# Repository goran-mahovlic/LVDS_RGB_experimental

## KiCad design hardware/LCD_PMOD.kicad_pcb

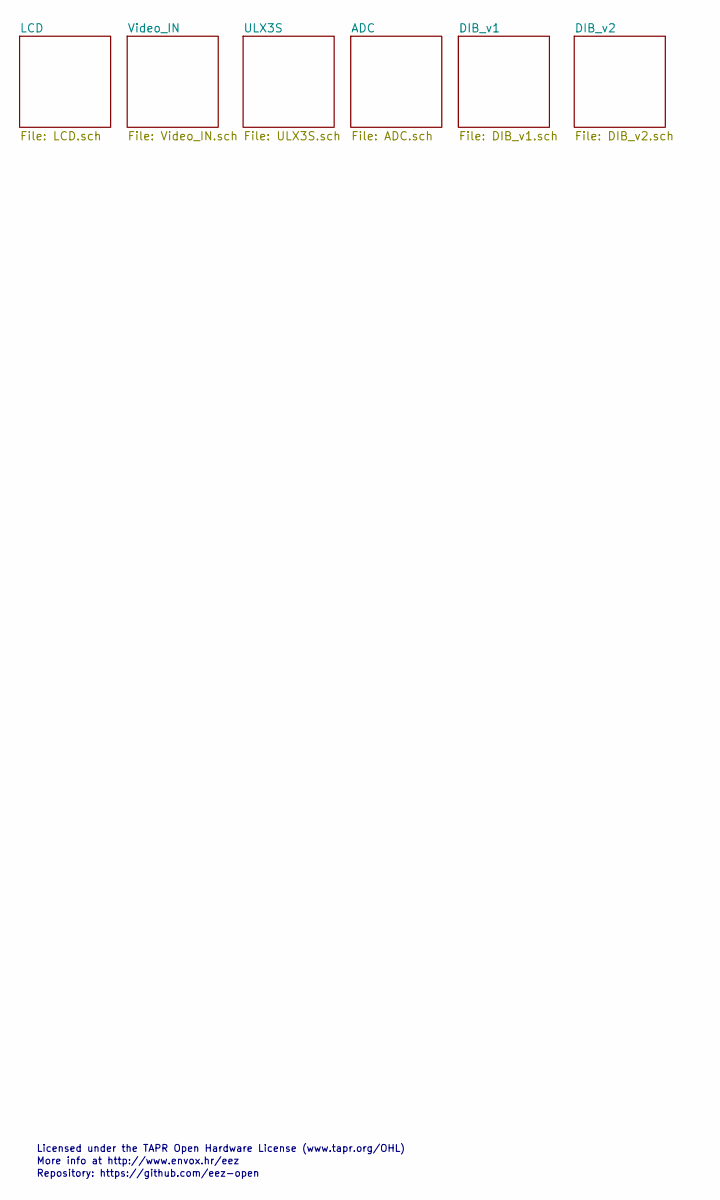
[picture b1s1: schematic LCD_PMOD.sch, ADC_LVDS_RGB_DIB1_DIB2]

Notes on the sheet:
Licensed under the TAPR Open Hardware License (www.tapr.org/OHL)
Repository: https://github.com/eez-open
More info at http://www.envox.hr/eez

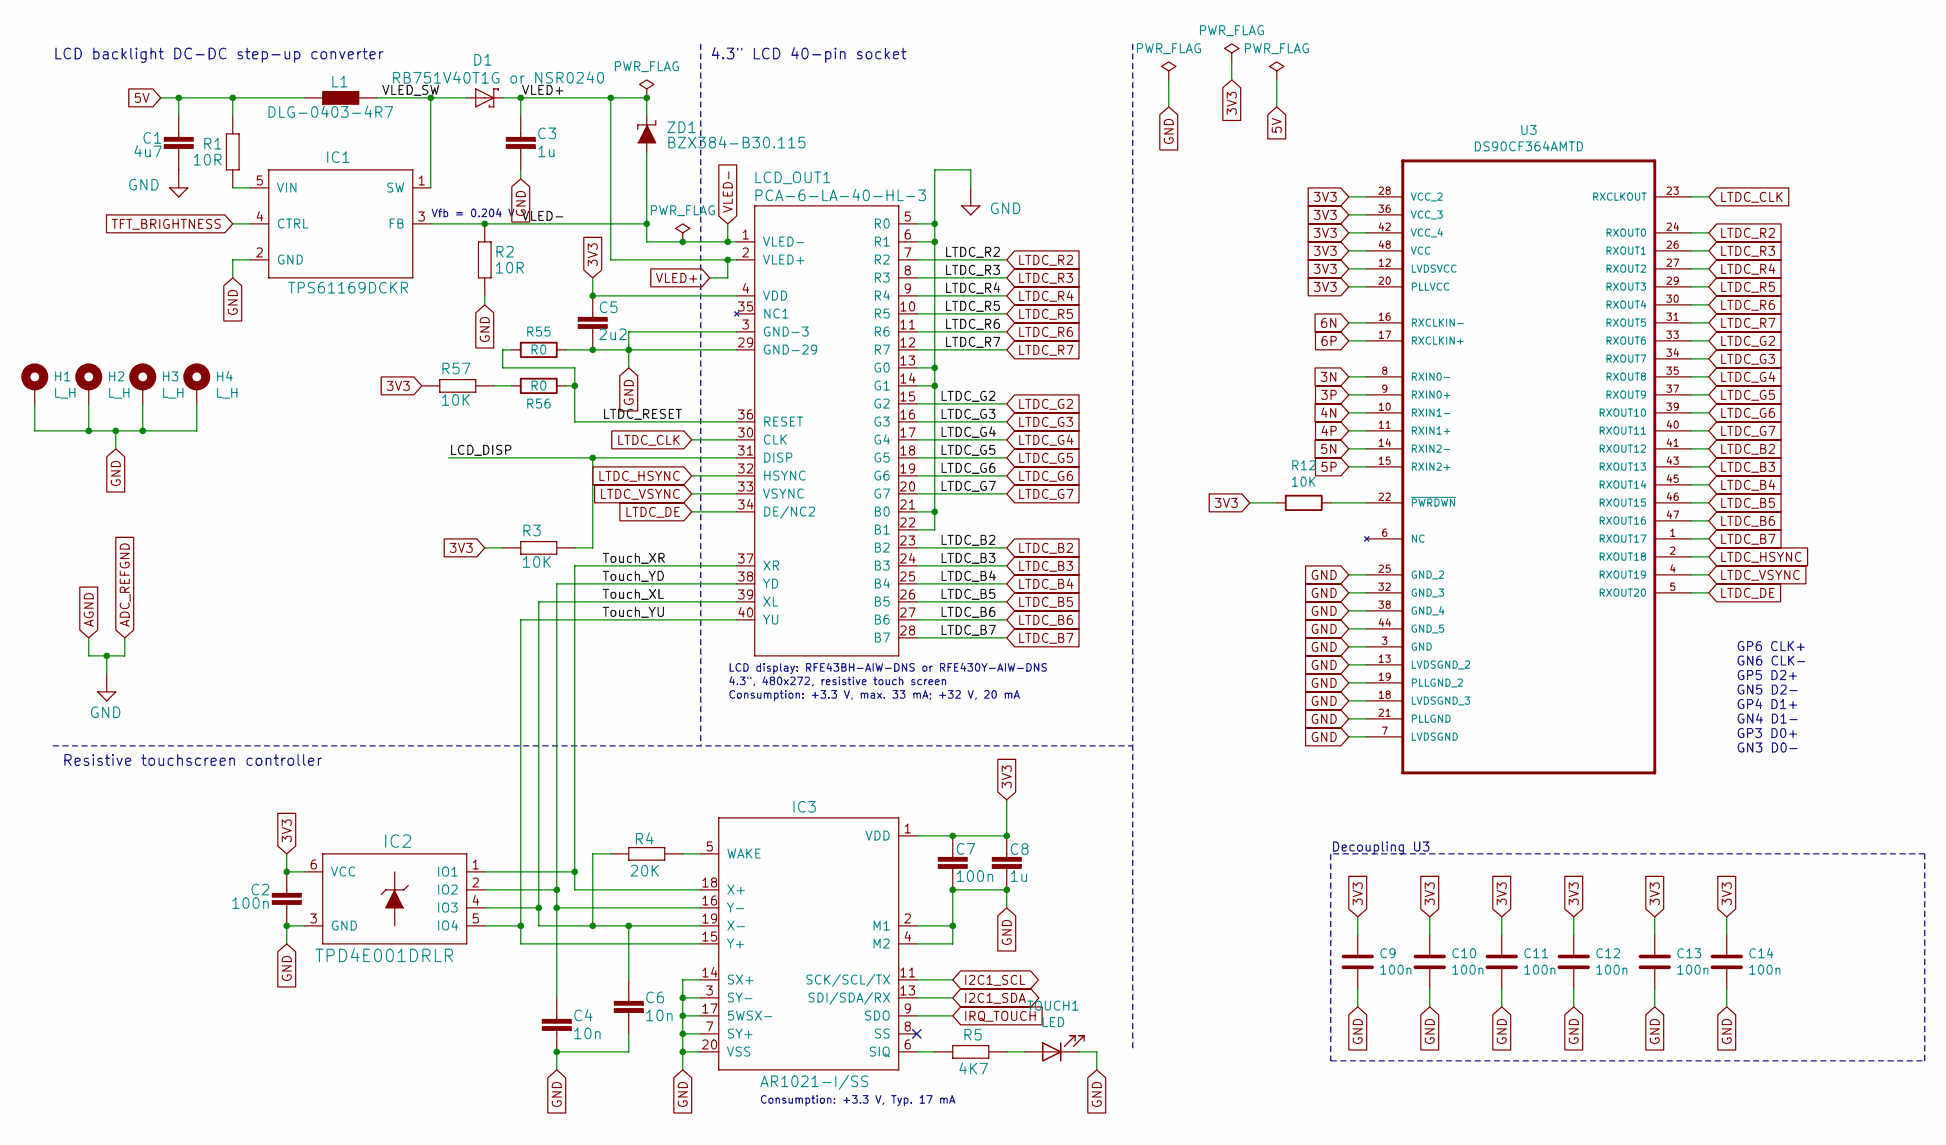
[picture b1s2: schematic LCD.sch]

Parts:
C1: 4u7; C_1206_3216Metric
C2, C7, C9, C10, C11, C12, C13, C14: 100n; C_0603_1608Metric
C3, C8: 1u; C_0805_2012Metric
C4, C6: 10n; C_0805_2012Metric
C5: 2u2; C_0805_2012Metric
D1: RB751V40T1G or NSR0240; SOD323-R
H1, H2, H3, H4: L_H; MountingHole_3.5mm_Pad_Via
IC1: TPS61169DCKR; DCK5
IC2: TPD4E001DRLR; DRL6
IC3: AR1021-I/SS; SOP65P780X200-20N
L1: DLG-0403-4R7; DE0403
LCD_OUT1: PCA-6-LA-40-HL-3; FPC_40
R1, R2: 10R; R_0805_2012Metric
R3, R12, R57: 10K; R_0805_2012Metric
R4: 20K; R_0805_2012Metric
R5: 4K7; R_0805_2012Metric
R55, R56: R0; R_0201_0603Metric
TOUCH1: LED; LED_0603_1608Metric
U3: DS90CF364AMTD; SOP50P800X110-48N
ZD1: BZX384-B30.115; SOD323-W

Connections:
3N: U3.8 (RXIN0-); also elsewhere on the board
3P: U3.9 (RXIN0+); also elsewhere on the board
3V3: C2.2, C5.1, C7.2, C8.2, C9.1, C10.1, C11.1, C12.1, C13.1, C14.1, IC2.6 (VCC), IC3.1 (VDD), LCD_OUT1.4 (VDD), R3.2, R12.2, R57.2, U3.12 (LVDSVCC), U3.20 (PLLVCC), U3.28 (VCC_2), U3.36 (VCC_3), U3.42 (VCC_4), U3.48 (VCC); also elsewhere on the board
4N: U3.10 (RXIN1-); also elsewhere on the board
4P: U3.11 (RXIN1+); also elsewhere on the board
5N: U3.14 (RXIN2-); also elsewhere on the board
5P: U3.15 (RXIN2+); also elsewhere on the board
5V: C1.1, L1.1, R1.1; also elsewhere on the board
6N: U3.16 (RXCLKIN-); also elsewhere on the board
6P: U3.17 (RXCLKIN+); also elsewhere on the board
8N: IC1.4 (CTRL); also elsewhere on the board
/LCD/LCD_DISP: LCD_OUT1.31 (DISP), R3.1
/LCD/LTDC_RESET: LCD_OUT1.36 (RESET), R55.2, R56.1
/LCD/Touch_XL: C6.1, IC2.4 (IO3), IC3.19 (X-), LCD_OUT1.39 (XL), R4.2
/LCD/Touch_XR: IC2.1 (IO1), IC3.18 (X+), LCD_OUT1.37 (XR)
/LCD/Touch_YD: C4.1, IC2.2 (IO2), IC3.16 (Y-), LCD_OUT1.38 (YD)
/LCD/Touch_YU: IC2.5 (IO4), IC3.15 (Y+), LCD_OUT1.40 (YU)
/LCD/VLED_SW: D1.A, IC1.1 (SW), L1.2
GND: C1.2, C2.1, C3.2, C4.2, C5.2, C6.2, C7.1, C8.1, C9.2, C10.2, C11.2, C12.2, C13.2, C14.2, H1.1, H2.1, H3.1, H4.1, IC1.2 (GND), IC2.3 (GND), IC3.2 (M1), IC3.3 (SY-), IC3.4 (M2), IC3.7 (SY+), IC3.14 (SX+), IC3.17 (5WSX-), IC3.20 (VSS), LCD_OUT1.3 (GND-3), LCD_OUT1.5 (R0), LCD_OUT1.6 (R1), LCD_OUT1.13 (G0), LCD_OUT1.14 (G1), LCD_OUT1.21 (B0), LCD_OUT1.22 (B1), LCD_OUT1.29 (GND-29), R2.2, R55.1, TOUCH1.1 (K), U3.3 (GND), U3.7 (LVDSGND), U3.13 (LVDSGND_2), U3.18 (LVDSGND_3), U3.19 (PLLGND_2), U3.21 (PLLGND), U3.25 (GND_2), U3.32 (GND_3), U3.38 (GND_4), U3.44 (GND_5); also elsewhere on the board
I2C1_SCL: IC3.11 (SCK/SCL/TX); also elsewhere on the board
I2C1_SDA: IC3.13 (SDI/SDA/RX); also elsewhere on the board
IRQ_TOUCH: IC3.9 (SDO); also elsewhere on the board
LTDC_B2: LCD_OUT1.23 (B2), U3.41 (RXOUT12)
LTDC_B3: LCD_OUT1.24 (B3), U3.43 (RXOUT13)
LTDC_B4: LCD_OUT1.25 (B4), U3.45 (RXOUT14)
LTDC_B5: LCD_OUT1.26 (B5), U3.46 (RXOUT15)
LTDC_B6: LCD_OUT1.27 (B6), U3.47 (RXOUT16)
LTDC_B7: LCD_OUT1.28 (B7), U3.1 (RXOUT17)
LTDC_CLK: LCD_OUT1.30 (CLK), U3.23 (RXCLKOUT)
LTDC_DE: LCD_OUT1.34 (DE/NC2), U3.5 (RXOUT20)
LTDC_G2: LCD_OUT1.15 (G2), U3.33 (RXOUT6)
LTDC_G3: LCD_OUT1.16 (G3), U3.34 (RXOUT7)
LTDC_G4: LCD_OUT1.17 (G4), U3.35 (RXOUT8)
LTDC_G5: LCD_OUT1.18 (G5), U3.37 (RXOUT9)
LTDC_G6: LCD_OUT1.19 (G6), U3.39 (RXOUT10)
LTDC_G7: LCD_OUT1.20 (G7), U3.40 (RXOUT11)
LTDC_HSYNC: LCD_OUT1.32 (HSYNC), U3.2 (RXOUT18)
LTDC_R2: LCD_OUT1.7 (R2), U3.24 (RXOUT0)
LTDC_R3: LCD_OUT1.8 (R3), U3.26 (RXOUT1)
LTDC_R4: LCD_OUT1.9 (R4), U3.27 (RXOUT2)
LTDC_R5: LCD_OUT1.10 (R5), U3.29 (RXOUT3)
LTDC_R6: LCD_OUT1.11 (R6), U3.30 (RXOUT4)
LTDC_R7: LCD_OUT1.12 (R7), U3.31 (RXOUT5)
LTDC_VSYNC: LCD_OUT1.33 (VSYNC), U3.4 (RXOUT19)
unnamed: IC1.5 (VIN), R1.2
unnamed: IC3.5 (WAKE), R4.1
unnamed: IC3.6 (SIQ), R5.2
unnamed: R5.1, TOUCH1.2 (A)
unnamed: R12.1, U3.22 (~PWRDWN)
unnamed: R56.2, R57.1
VLED+: C3.1, D1.C, LCD_OUT1.2 (VLED+), ZD1.C; also elsewhere on the board
VLED-: IC1.3 (FB), LCD_OUT1.1 (VLED-), R2.1, ZD1.A; also elsewhere on the board

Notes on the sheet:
4.3" LCD 40-pin socket
LCD backlight DC-DC step-up converter
Consumption: +3.3 V, Typ. 17 mA
Consumption: +3.3 V, max. 33 mA; +32 V, 20 mA
Vfb = 0.204 V
LCD display: RFE43BH-AIW-DNS or RFE430Y-AIW-DNS
4.3", 480x272, resistive touch screen
Resistive touchscreen controller
GP6 CLK+ GN6 CLK- GP5 D2+ GN5 D2- GP4 D1+ GN4 D1- GP3 D0+ GN3 D0-
Decoupling U3

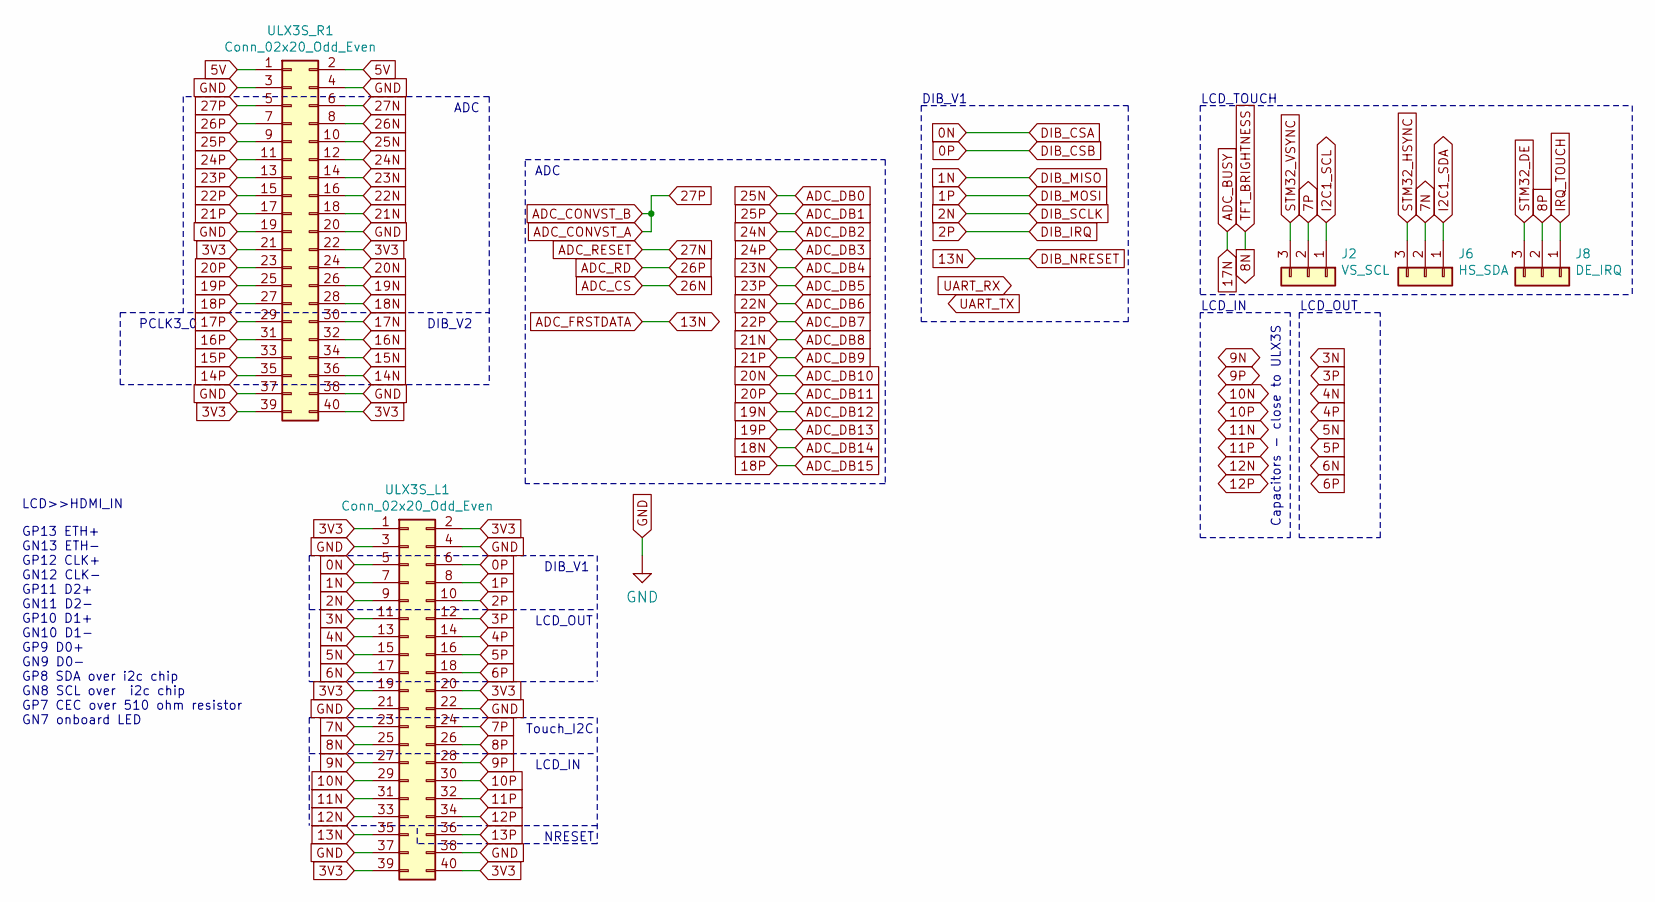
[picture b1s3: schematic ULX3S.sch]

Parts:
J2: VS_SCL; PinHeader_1x03_P2.00mm_Vertical
J6: HS_SDA; PinHeader_1x03_P2.00mm_Vertical
J8: DE_IRQ; PinHeader_1x03_P2.00mm_Vertical
ULX3S_L1, ULX3S_R1: Conn_02x20_Odd_Even; PinSocket_2x20_P2.54mm_Vertical

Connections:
0N: ULX3S_L1.5; also elsewhere on the board
0P: ULX3S_L1.6; also elsewhere on the board
1N: ULX3S_L1.7; also elsewhere on the board
1P: ULX3S_L1.8; also elsewhere on the board
2N: ULX3S_L1.9; also elsewhere on the board
2P: ULX3S_L1.10; also elsewhere on the board
3N: ULX3S_L1.11; also elsewhere on the board
3P: ULX3S_L1.12; also elsewhere on the board
3V3: ULX3S_L1.1, ULX3S_L1.2, ULX3S_L1.19, ULX3S_L1.20, ULX3S_L1.39, ULX3S_L1.40, ULX3S_R1.21, ULX3S_R1.22, ULX3S_R1.39, ULX3S_R1.40; also elsewhere on the board
4N: ULX3S_L1.13; also elsewhere on the board
4P: ULX3S_L1.14; also elsewhere on the board
5N: ULX3S_L1.15; also elsewhere on the board
5P: ULX3S_L1.16; also elsewhere on the board
5V: ULX3S_R1.1, ULX3S_R1.2; also elsewhere on the board
6N: ULX3S_L1.17; also elsewhere on the board
6P: ULX3S_L1.18; also elsewhere on the board
7N: J6.2, ULX3S_L1.23
7P: J2.2, ULX3S_L1.24
8N: ULX3S_L1.25; also elsewhere on the board
8P: J8.2, ULX3S_L1.26
9N: ULX3S_L1.27; also elsewhere on the board
9P: ULX3S_L1.28; also elsewhere on the board
10N: ULX3S_L1.29; also elsewhere on the board
10P: ULX3S_L1.30; also elsewhere on the board
11N: ULX3S_L1.31; also elsewhere on the board
11P: ULX3S_L1.32; also elsewhere on the board
12N: ULX3S_L1.33; also elsewhere on the board
12P: ULX3S_L1.34; also elsewhere on the board
13N: ULX3S_L1.35; also elsewhere on the board
14N: ULX3S_R1.36; also elsewhere on the board
14P: ULX3S_R1.35; also elsewhere on the board
15N: ULX3S_R1.34; also elsewhere on the board
15P: ULX3S_R1.33; also elsewhere on the board
16N: ULX3S_R1.32; also elsewhere on the board
16P: ULX3S_R1.31; also elsewhere on the board
17N: ULX3S_R1.30; also elsewhere on the board
17P: ULX3S_R1.29; also elsewhere on the board
18N: ULX3S_R1.28; also elsewhere on the board
18P: ULX3S_R1.27; also elsewhere on the board
19N: ULX3S_R1.26; also elsewhere on the board
19P: ULX3S_R1.25; also elsewhere on the board
20N: ULX3S_R1.24; also elsewhere on the board
20P: ULX3S_R1.23; also elsewhere on the board
21N: ULX3S_R1.18; also elsewhere on the board
21P: ULX3S_R1.17; also elsewhere on the board
22N: ULX3S_R1.16; also elsewhere on the board
22P: ULX3S_R1.15; also elsewhere on the board
23N: ULX3S_R1.14; also elsewhere on the board
23P: ULX3S_R1.13; also elsewhere on the board
24N: ULX3S_R1.12; also elsewhere on the board
24P: ULX3S_R1.11; also elsewhere on the board
25N: ULX3S_R1.10; also elsewhere on the board
25P: ULX3S_R1.9; also elsewhere on the board
26N: ULX3S_R1.8; also elsewhere on the board
26P: ULX3S_R1.7; also elsewhere on the board
27N: ULX3S_R1.6; also elsewhere on the board
27P: ULX3S_R1.5; also elsewhere on the board
GND: ULX3S_L1.3, ULX3S_L1.4, ULX3S_L1.21, ULX3S_L1.22, ULX3S_L1.37, ULX3S_L1.38, ULX3S_R1.3, ULX3S_R1.4, ULX3S_R1.19, ULX3S_R1.20, ULX3S_R1.37, ULX3S_R1.38; also elsewhere on the board
I2C1_SCL: J2.1; also elsewhere on the board
I2C1_SDA: J6.1; also elsewhere on the board
IRQ_TOUCH: J8.1; also elsewhere on the board
STM32_DE: J8.3; also elsewhere on the board
STM32_HSYNC: J6.3; also elsewhere on the board
STM32_VSYNC: J2.3; also elsewhere on the board

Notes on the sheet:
GP13 ETH+ GN13 ETH- GP12 CLK+ GN12 CLK- GP11 D2+ GN11 D2- GP10 D1+ GN10 D1- GP9 D0+ GN9 D0- GP8 SDA over i2c chip GN8 SCL over i2c chip GP7 CEC over 510 ohm resistor GN7 onboard LED
LCD>>HDMI_IN
DIB_V1
LCD_TOUCH
Capacitors - close to ULX3S
LCD_IN
LCD_OUT
Touch_I2C
ADC
NRESET
PCLK3_0
DIB_V2

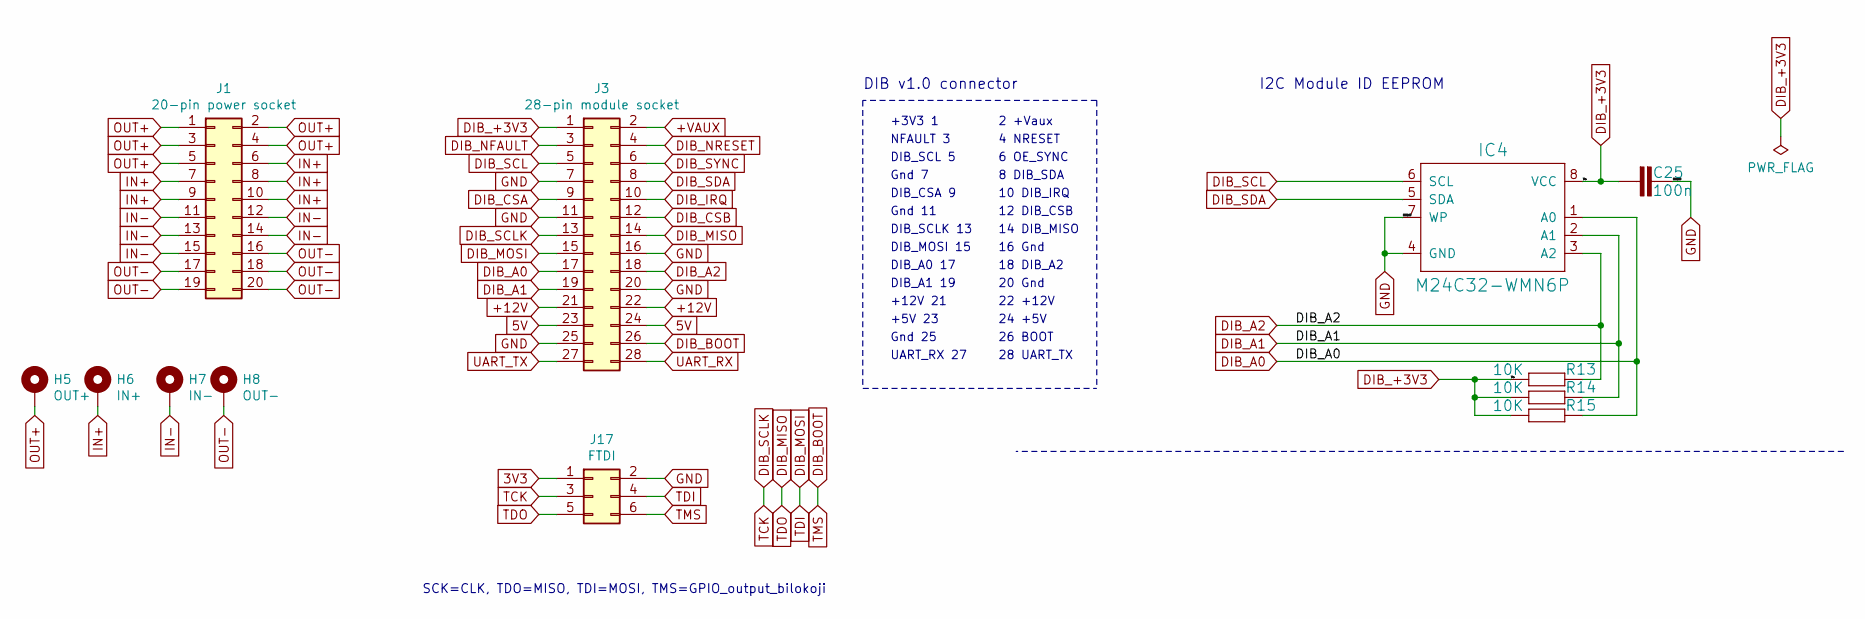
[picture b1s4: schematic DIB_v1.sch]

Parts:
C25: 100n; C_0603_1608Metric
H5: OUT+; MountingHole_2.2mm_M2_Pad
H6: IN+; MountingHole_2.2mm_M2_Pad
H7: IN-; MountingHole_2.2mm_M2_Pad
H8: OUT-; MountingHole_2.2mm_M2_Pad
IC4: M24C32-WMN6P; SOIC127P600X170-9N
J1: 20-pin power socket; PinSocket_2x10_P2.54mm_Horizontal_DIB_V1
J3: 28-pin module socket; PinHeader_2x14_P2.54mm_Horizontal_DIB_V1
J17: FTDI; PinHeader_2x03_P2.54mm_Vertical
R13, R14, R15: 10K; C_0805_2012Metric

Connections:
0N: J3.9; also elsewhere on the board
0P: J3.12; also elsewhere on the board
1N: J3.14, J17.5; also elsewhere on the board
1P: J3.15, J17.4; also elsewhere on the board
2N: J3.13, J17.3; also elsewhere on the board
2P: J3.10; also elsewhere on the board
3V3: J17.1; also elsewhere on the board
5V: J3.23, J3.24; also elsewhere on the board
DIB_+3V3: C25.2, IC4.8 (VCC), J3.1, R13.1, R14.1, R15.1
DIB_A0: IC4.1 (A0), J3.17, R15.2
DIB_A1: IC4.2 (A1), J3.19, R14.2
DIB_A2: IC4.3 (A2), J3.18, R13.2
DIB_BOOT: J3.26, J17.6
DIB_SCL: IC4.6 (SCL), J3.5
DIB_SDA: IC4.5 (SDA), J3.8
GND: C25.1, IC4.4 (GND), IC4.7 (WP), J3.7, J3.11, J3.16, J3.20, J3.25, J17.2; also elsewhere on the board
IN+: H6.1, J1.6, J1.7, J1.8, J1.9, J1.10
IN-: H7.1, J1.11, J1.12, J1.13, J1.14, J1.15
OUT+: H5.1, J1.1, J1.2, J1.3, J1.4, J1.5
OUT-: H8.1, J1.16, J1.17, J1.18, J1.19, J1.20

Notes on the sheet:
26 BOOT
Gnd 7
22 +12V
16 Gnd
6 OE_SYNC
24 +5V
+5V 23
Gnd 25
+12V 21
10 DIB_IRQ
DIB_CSA 9
2 +Vaux
12 DIB_CSB
+3V3 1
Gnd 11
8 DIB_SDA
DIB_SCL 5
DIB_A1 19
4 NRESET
DIB_A0 17
20 Gnd
NFAULT 3
14 DIB_MISO
DIB_MOSI 15
DIB_SCLK 13
18 DIB_A2
UART_RX 27
28 UART_TX
DIB v1.0 connector
I2C Module ID EEPROM
SCK=CLK, TDO=MISO, TDI=MOSI, TMS=GPIO_output_bilokoji

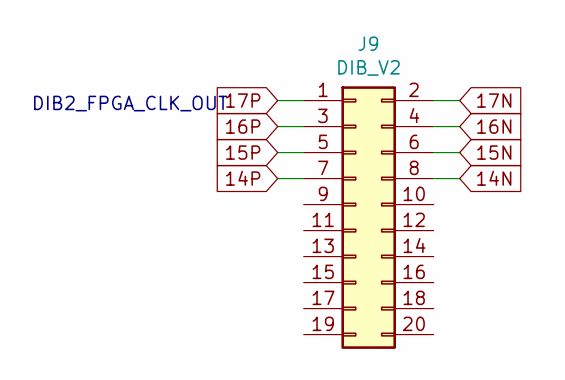
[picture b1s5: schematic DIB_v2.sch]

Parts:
J9: DIB_V2; PinHeader_2x10_P2.54mm_Horizontal

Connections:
14N: J9.8; also elsewhere on the board
14P: J9.7; also elsewhere on the board
15N: J9.6; also elsewhere on the board
15P: J9.5; also elsewhere on the board
16N: J9.4; also elsewhere on the board
16P: J9.3; also elsewhere on the board
17N: J9.2; also elsewhere on the board
17P: J9.1; also elsewhere on the board

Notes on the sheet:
DIB2_FPGA_CLK_OUT

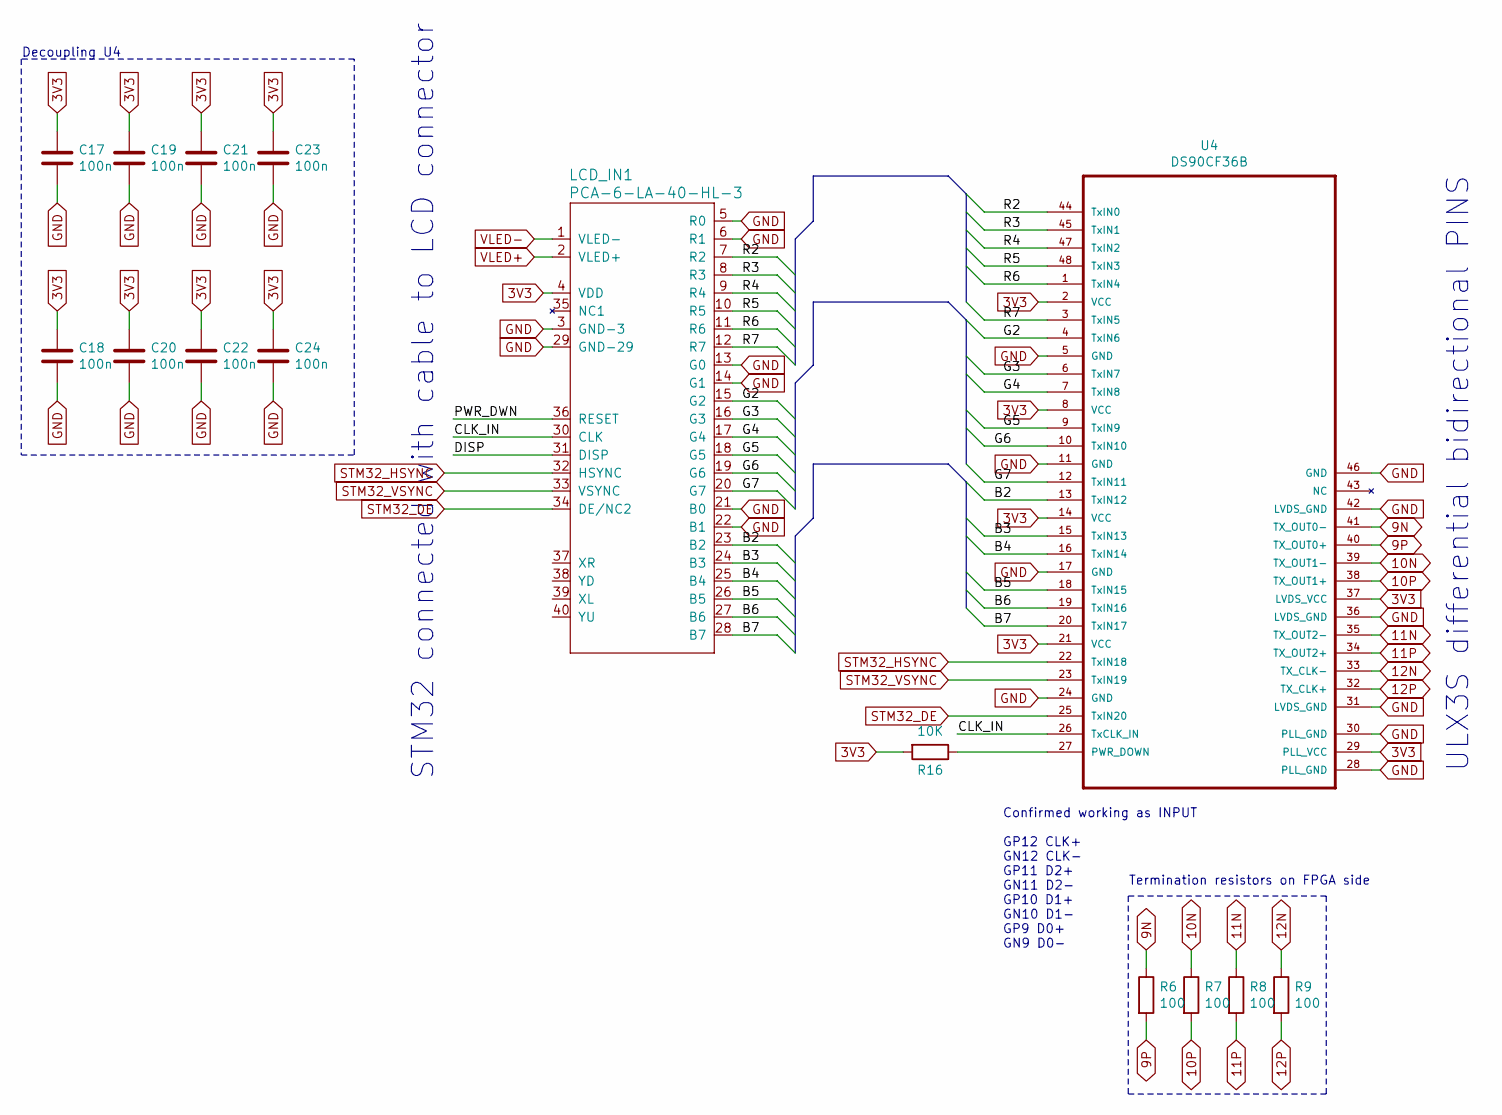
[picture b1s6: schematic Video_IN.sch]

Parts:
C17, C18, C19, C20, C21, C22, C23, C24: 100n; C_0603_1608Metric
LCD_IN1: PCA-6-LA-40-HL-3; FPC_40
R6, R7, R8, R9: 100; R_0805_2012Metric
R16: 10K; R_0805_2012Metric
U4: DS90CF36B; SOP50P800X110-48N

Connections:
3V3: C17.1, C18.1, C19.1, C20.1, C21.1, C22.1, C23.1, C24.1, LCD_IN1.4 (VDD), R16.2, U4.2 (VCC), U4.8 (VCC), U4.14 (VCC), U4.21 (VCC), U4.29 (PLL_VCC), U4.37 (LVDS_VCC); also elsewhere on the board
9N: R6.1, U4.41 (TX_OUT0-); also elsewhere on the board
9P: R6.2, U4.40 (TX_OUT0+); also elsewhere on the board
10N: R7.1, U4.39 (TX_OUT1-); also elsewhere on the board
10P: R7.2, U4.38 (TX_OUT1+); also elsewhere on the board
11N: R8.1, U4.35 (TX_OUT2-); also elsewhere on the board
11P: R8.2, U4.34 (TX_OUT2+); also elsewhere on the board
12N: R9.1, U4.33 (TX_CLK-); also elsewhere on the board
12P: R9.2, U4.32 (TX_CLK+); also elsewhere on the board
/Video_IN/B2: LCD_IN1.23 (B2), U4.13 (TxIN12)
/Video_IN/B3: LCD_IN1.24 (B3), U4.15 (TxIN13)
/Video_IN/B4: LCD_IN1.25 (B4), U4.16 (TxIN14)
/Video_IN/B5: LCD_IN1.26 (B5), U4.18 (TxIN15)
/Video_IN/B6: LCD_IN1.27 (B6), U4.19 (TxIN16)
/Video_IN/B7: LCD_IN1.28 (B7), U4.20 (TxIN17)
/Video_IN/G2: LCD_IN1.15 (G2), U4.4 (TxIN6)
/Video_IN/G3: LCD_IN1.16 (G3), U4.6 (TxIN7)
/Video_IN/G4: LCD_IN1.17 (G4), U4.7 (TxIN8)
/Video_IN/G5: LCD_IN1.18 (G5), U4.9 (TxIN9)
/Video_IN/G6: LCD_IN1.19 (G6), U4.10 (TxIN10)
/Video_IN/G7: LCD_IN1.20 (G7), U4.12 (TxIN11)
/Video_IN/R2: LCD_IN1.7 (R2), U4.44 (TxIN0)
/Video_IN/R3: LCD_IN1.8 (R3), U4.45 (TxIN1)
/Video_IN/R4: LCD_IN1.9 (R4), U4.47 (TxIN2)
/Video_IN/R5: LCD_IN1.10 (R5), U4.48 (TxIN3)
/Video_IN/R6: LCD_IN1.11 (R6), U4.1 (TxIN4)
/Video_IN/R7: LCD_IN1.12 (R7), U4.3 (TxIN5)
GND: C17.2, C18.2, C19.2, C20.2, C21.2, C22.2, C23.2, C24.2, LCD_IN1.3 (GND-3), LCD_IN1.5 (R0), LCD_IN1.6 (R1), LCD_IN1.13 (G0), LCD_IN1.14 (G1), LCD_IN1.21 (B0), LCD_IN1.22 (B1), LCD_IN1.29 (GND-29), U4.5 (GND), U4.11 (GND), U4.17 (GND), U4.24 (GND), U4.28 (PLL_GND), U4.30 (PLL_GND), U4.31 (LVDS_GND), U4.36 (LVDS_GND), U4.42 (LVDS_GND), U4.46 (GND); also elsewhere on the board
STM32_CLK_IN: LCD_IN1.30 (CLK), U4.26 (TxCLK_IN)
STM32_DE: LCD_IN1.34 (DE/NC2), U4.25 (TxIN20); also elsewhere on the board
STM32_HSYNC: LCD_IN1.32 (HSYNC), U4.22 (TxIN18); also elsewhere on the board
STM32_VSYNC: LCD_IN1.33 (VSYNC), U4.23 (TxIN19); also elsewhere on the board
VLED+: LCD_IN1.2 (VLED+); also elsewhere on the board
VLED-: LCD_IN1.1 (VLED-); also elsewhere on the board

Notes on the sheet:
Confirmed working as INPUT GP12 CLK+ GN12 CLK- GP11 D2+ GN11 D2- GP10 D1+ GN10 D1- GP9 D0+ GN9 D0-
STM32 connected with cable to LCD connector
ULX3S differential bidirectional PINS
Decoupling U4
Termination resistors on FPGA side

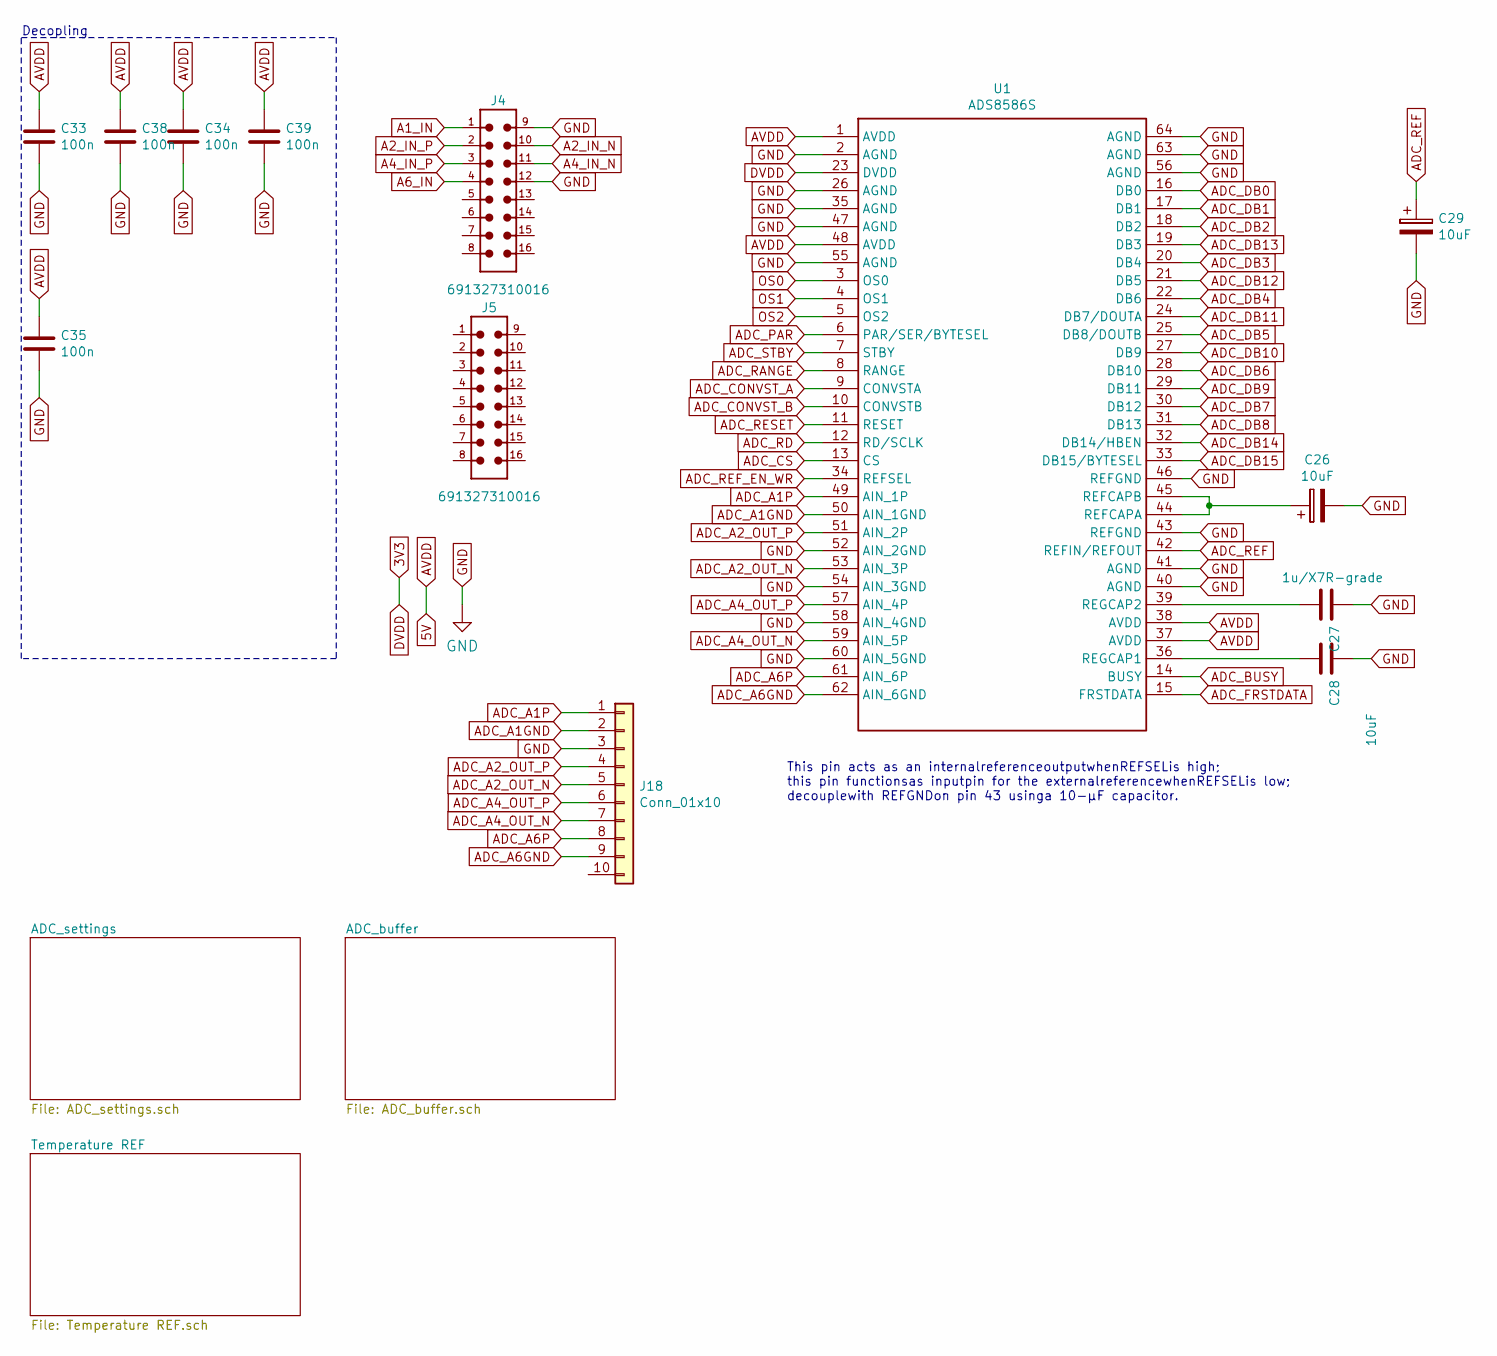
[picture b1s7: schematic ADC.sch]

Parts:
C26, C28, C29: 10uF; C_0805_2012Metric
C27: 1u/X7R-grade; C_0805_2012Metric
C33, C34, C35, C38, C39: 100n; C_0603_1608Metric
J4, J5: 691327310016
J18: Conn_01x10; PinHeader_1x10_P1.00mm_Vertical
U1: ADS8586S; LQFP-64_10x10mm_P0.5mm

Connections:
3V3: U1.23 (DVDD); also elsewhere on the board
5V: C33.1, C34.1, C35.1, C38.1, C39.1, U1.1 (AVDD), U1.37 (AVDD), U1.38 (AVDD), U1.48 (AVDD); also elsewhere on the board
13N: U1.15 (FRSTDATA); also elsewhere on the board
17N: U1.14 (BUSY); also elsewhere on the board
18N: U1.32 (DB14/HBEN); also elsewhere on the board
18P: U1.33 (DB15/BYTESEL); also elsewhere on the board
19N: U1.21 (DB5); also elsewhere on the board
19P: U1.19 (DB3); also elsewhere on the board
20N: U1.27 (DB9); also elsewhere on the board
20P: U1.24 (DB7/DOUTA); also elsewhere on the board
21N: U1.31 (DB13); also elsewhere on the board
21P: U1.29 (DB11); also elsewhere on the board
22N: U1.28 (DB10); also elsewhere on the board
22P: U1.30 (DB12); also elsewhere on the board
23N: U1.22 (DB6); also elsewhere on the board
23P: U1.25 (DB8/DOUTB); also elsewhere on the board
24N: U1.18 (DB2); also elsewhere on the board
24P: U1.20 (DB4); also elsewhere on the board
25N: U1.16 (DB0); also elsewhere on the board
25P: U1.17 (DB1); also elsewhere on the board
26N: U1.13 (CS); also elsewhere on the board
26P: U1.12 (RD/SCLK); also elsewhere on the board
27N: U1.11 (RESET); also elsewhere on the board
27P: U1.9 (CONVSTA), U1.10 (CONVSTB); also elsewhere on the board
A1_IN: J4.1; also elsewhere on the board
A2_IN_N: J4.10; also elsewhere on the board
A2_IN_P: J4.2; also elsewhere on the board
A4_IN_N: J4.11; also elsewhere on the board
A4_IN_P: J4.3; also elsewhere on the board
A6_IN: J4.4; also elsewhere on the board
ADC_A1GND: J18.2, U1.50 (AIN_1GND); also elsewhere on the board
ADC_A1P: J18.1, U1.49 (AIN_1P); also elsewhere on the board
ADC_A2_OUT_N: J18.5, U1.53 (AIN_3P); also elsewhere on the board
ADC_A2_OUT_P: J18.4, U1.51 (AIN_2P); also elsewhere on the board
ADC_A4_OUT_N: J18.7, U1.59 (AIN_5P); also elsewhere on the board
ADC_A4_OUT_P: J18.6, U1.57 (AIN_4P); also elsewhere on the board
ADC_A6GND: J18.9, U1.62 (AIN_6GND); also elsewhere on the board
ADC_A6P: J18.8, U1.61 (AIN_6P); also elsewhere on the board
ADC_PAR: U1.6 (PAR/SER/BYTESEL); also elsewhere on the board
ADC_RANGE: U1.8 (RANGE); also elsewhere on the board
ADC_REF: C29.1, U1.42 (REFIN/REFOUT); also elsewhere on the board
ADC_REF_EN_WR: U1.34 (REFSEL); also elsewhere on the board
ADC_STBY: U1.7 (STBY); also elsewhere on the board
GND: C26.2, C27.1, C28.1, C29.2, C33.2, C34.2, C35.2, C38.2, C39.2, J4.9, J4.12, J18.3, U1.2 (AGND), U1.26 (AGND), U1.35 (AGND), U1.40 (AGND), U1.41 (AGND), U1.43 (REFGND), U1.46 (REFGND), U1.47 (AGND), U1.52 (AIN_2GND), U1.54 (AIN_3GND), U1.55 (AGND), U1.56 (AGND), U1.58 (AIN_4GND), U1.60 (AIN_5GND), U1.63 (AGND), U1.64 (AGND); also elsewhere on the board
unnamed: C26.1, U1.44 (REFCAPA), U1.45 (REFCAPB)
unnamed: C27.2, U1.39 (REGCAP2)
unnamed: C28.2, U1.36 (REGCAP1)
OS0: U1.3 (OS0); also elsewhere on the board
OS1: U1.4 (OS1); also elsewhere on the board
OS2: U1.5 (OS2); also elsewhere on the board

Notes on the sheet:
Decopling
This pin acts as an internalreferenceoutputwhenREFSELis high; this pin functionsas inputpin for the externalreferencewhenREFSELis low; decouplewith REFGNDon pin 43 usinga 10-μF capacitor.

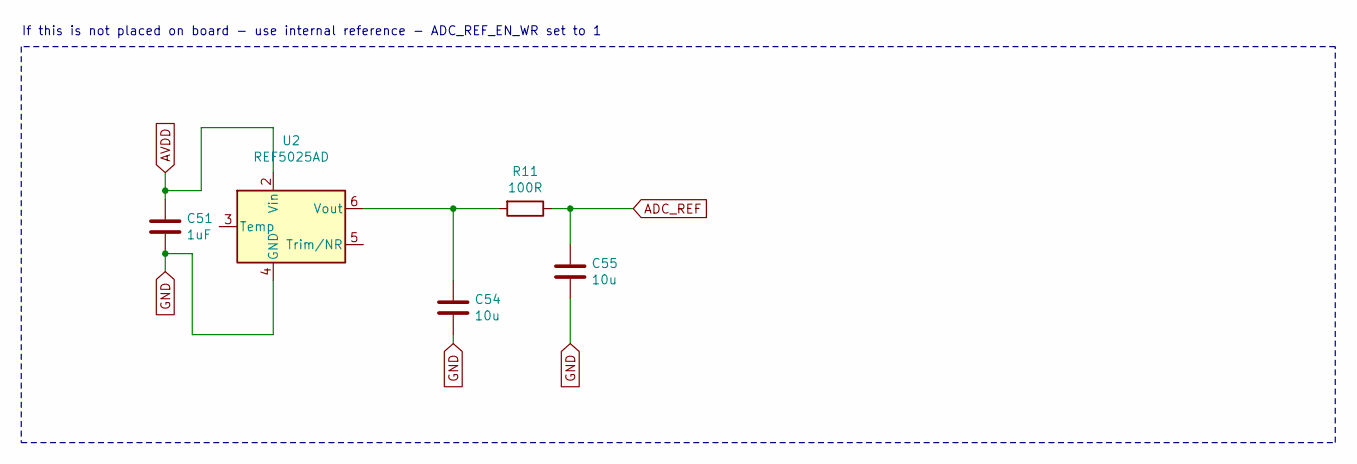
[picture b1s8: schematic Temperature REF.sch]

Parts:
C51: 1uF; C_0603_1608Metric
C54, C55: 10u; C_0603_1608Metric
R11: 100R; R_0805_2012Metric
U2: REF5025AD; SOIC-8_3.9x4.9mm_P1.27mm

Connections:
5V: C51.1, U2.2 (Vin); also elsewhere on the board
ADC_REF: C55.1, R11.1; also elsewhere on the board
GND: C51.2, C54.2, C55.2, U2.4 (GND); also elsewhere on the board
unnamed 159: U2.5 (Trim/NR); also elsewhere on the board
unnamed: C54.1, R11.2, U2.6 (Vout)

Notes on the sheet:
If this is not placed on board - use internal reference - ADC_REF_EN_WR set to 1

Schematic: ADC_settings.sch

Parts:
J10: OS0; PinHeader_1x03_P2.00mm_Vertical
J11: OS1; PinHeader_1x03_P2.00mm_Vertical
J12: OS2; PinHeader_1x03_P2.00mm_Vertical
J13: PAR; PinHeader_1x03_P2.00mm_Vertical
J14: RANGE; PinHeader_1x03_P2.00mm_Vertical
J15: REF; PinHeader_1x03_P2.00mm_Vertical
R17, R18, R19, R20, R21, R22, R23: 1K; R_0805_2012Metric

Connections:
5V: J10.3, J11.3, J12.3, J13.3, J14.3, J15.3, R23.2; also elsewhere on the board
ADC_PAR: R20.1; also elsewhere on the board
ADC_RANGE: R21.1; also elsewhere on the board
ADC_REF_EN_WR: R22.1; also elsewhere on the board
ADC_STBY: R23.1; also elsewhere on the board
GND: J10.1, J11.1, J12.1, J13.1, J14.1, J15.1; also elsewhere on the board
unnamed: J10.2, R17.2
unnamed: J11.2, R18.2
unnamed: J12.2, R19.2
unnamed: J13.2, R20.2
unnamed: J14.2, R21.2
unnamed: J15.2, R22.2
OS0: R17.1; also elsewhere on the board
OS1: R18.1; also elsewhere on the board
OS2: R19.1; also elsewhere on the board

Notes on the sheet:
PAR(0)/SER(1)
+-5(0)/+-10(1)
(1)Enable internal REF
Oversampling

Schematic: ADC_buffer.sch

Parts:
C15, C16: 330n; C_0603_1608Metric
C30, C32, C40, C41: 100n; C_0603_1608Metric
C31: CP; C_0805_2012Metric
C36: CP; CP_EIA-3528-21_Kemet-B
C37: 1nF; C_0603_1608Metric
C42, C43, C44, C45: 10u; C_0603_1608Metric
C60, C61: NI; C_0603_1608Metric
C62: 370pF; C_0603_1608Metric
C63, C64: 470p; C_0603_1608Metric
C65, C66: 1n; C_0603_1608Metric
C67, C68, C69, C70: 270pF; C_0603_1608Metric
C71, C72: 22nF; C_0603_1608Metric
D2, D3, D4, D5, D6, D7: D_TVS; D_SOD-523
J7: JMP_A0; PinHeader_1x03_P2.00mm_Vertical
J16: TBA1E
L2, L3: L; C_0603_1608Metric
R24: 49R9; R_1206_3216Metric
R25: NI; R_0805_2012Metric
R26, R27, R50: 49R9; R_0805_2012Metric
R28, R29, R30, R31: 1K2; R_1206_3216Metric
R32, R35: 1K; R_0805_2012Metric
R33, R34, R36, R37: 300R; R_1206_3216Metric
R38, R39, R40, R41: 1K2; R_0805_2012Metric
R42, R43, R44, R45: 5R; R_0805_2012Metric
R46, R47, R48, R49: 10R; R_0805_2012Metric
R51, R52, R53, R54: 1K; R_1206_3216Metric
U5: MC78L05_SO8; SOIC-8_3.9x4.9mm_P1.27mm
U6: THS4032ID; SOIC127P600X173-8N
U7, U8: THS4551IDGKT; VSSOP-8_3.0x3.0mm_P0.65mm
U9: MC79L05_SO8; SOIC-8_3.9x4.9mm_P1.27mm

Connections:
5V: R32.1, R35.1, U7.3 (VS+), U8.3 (VS+); also elsewhere on the board
/ADC/ADC_buffer/A2N: C64.1, D4.1 (A1), R31.1, R37.2, R41.2
/ADC/ADC_buffer/A2P: C64.2, D3.1 (A1), R30.1, R36.2, R40.2
/ADC/ADC_buffer/A2_out2+: R40.1, R44.1, R48.2
/ADC/ADC_buffer/A2_out2-: R41.1, R45.1, R49.2
/ADC/ADC_buffer/A2_out+: C69.2, R44.2, U8.4 (OUT+)
/ADC/ADC_buffer/A2_out-: C70.2, R45.2, U8.5 (OUT-)
/ADC/ADC_buffer/A4N: C63.1, D7.1 (A1), R29.1, R34.2, R39.2
/ADC/ADC_buffer/A4P: C63.2, D6.1 (A1), R28.1, R33.2, R38.2
/ADC/ADC_buffer/A4_out2+: R38.1, R42.1, R46.2
/ADC/ADC_buffer/A4_out2-: R39.1, R43.1, R47.2
/ADC/ADC_buffer/A4_out+: C67.2, R42.2, U7.4 (OUT+)
/ADC/ADC_buffer/A4_out-: C68.2, R43.2, U7.5 (OUT-)
/ADC/ADC_buffer/U7N: C65.1, C68.1, R34.1, U7.1 (IN-)
/ADC/ADC_buffer/U7P: C65.2, C67.1, R33.1, U7.8 (IN+)
/ADC/ADC_buffer/U8N: C66.1, C70.1, R37.1, U8.1 (IN-)
/ADC/ADC_buffer/U8P: C66.2, C69.1, R36.1, U8.8 (IN+)
A1_IN: R53.2; also elsewhere on the board
A2_IN_N: R31.2; also elsewhere on the board
A2_IN_P: R30.2; also elsewhere on the board
A4_IN_N: R29.2; also elsewhere on the board
A4_IN_P: R28.2; also elsewhere on the board
A6_IN: R51.2; also elsewhere on the board
ADC_A1GND: C60.2, C62.2, R50.1; also elsewhere on the board
ADC_A1P: C62.1, R27.1; also elsewhere on the board
ADC_A2_OUT_N: C72.1, R49.1; also elsewhere on the board
ADC_A2_OUT_P: C72.2, R48.1; also elsewhere on the board
ADC_A4_OUT_N: C71.1, R47.1; also elsewhere on the board
ADC_A4_OUT_P: C71.2, R46.1; also elsewhere on the board
ADC_A6GND: C37.2, R54.1; also elsewhere on the board
ADC_A6P: C37.1, R52.1; also elsewhere on the board
GND: C15.2, C16.2, C30.2, C31.2, C32.2, C36.2, C40.2, C41.2, C42.2, C43.2, C44.2, C45.2, D2.2 (A2), D3.2 (A2), D4.2 (A2), D5.2 (A2), D6.2 (A2), D7.2 (A2), J16.2, J16.7, R25.1, R50.2, R54.2, U7.6 (VS-), U8.6 (VS-); also elsewhere on the board
HVDD_9V: C15.1, J16.6, U5.8 (IN)
HVSS_9V: C16.1, J16.5, U9.2 (IN), U9.3 (IN), U9.6 (IN), U9.7 (IN)
unnamed: C40.1, C42.1, L2.1, U5.1 (OUT)
unnamed: C41.1, C43.1, L3.1, U9.1 (OUT)
unnamed: C61.1, J7.3, R26.1, U6.1 (1OUT)
unnamed: C61.2, R25.2, R26.2, U6.2 (1IN-)
unnamed: D5.1 (A1), R51.1, R52.2
unnamed: J7.1, R27.2
unnamed: R32.2, U7.7 (~PD~)
unnamed: R35.2, U8.7 (~PD~)
unnamed: U5.2 (GND), U5.3 (GND), U5.6 (GND), U5.7 (GND), U9.5 (GND)

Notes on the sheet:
-9V
+9V
TBA1E
ADC_A1N bih dovukao na C60 i spojio ih s 49R9 na AGND od D2 tako da imamo sli?nu stvar kao za ADC_A6

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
